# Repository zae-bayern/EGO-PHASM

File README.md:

Open-Source Repository für das BMWE-finanzierte Mikroprojekt "EGO-PHASM" des ZAE Bayerns.

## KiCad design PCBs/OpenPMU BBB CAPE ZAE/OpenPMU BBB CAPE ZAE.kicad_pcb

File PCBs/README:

These are the modified versions of the PCBs from OpenPMU. A brief overview of the changes:
- The sensor part has been adapted to 230V and 16A at 50Hz.
- The communication between sensor and measurement computer is digital now. All analog related circuitry is now on the Sensor Board only.
- The power and communication lines between the sensor board and the sensor cape has been secured with an isolation transformer and optocouplers.

The original OpenPMU project can be found here: https://www.openpmu.org/

It is highly recommended that this project is constructed and operated exclusively by qualified personnel!
This project is provided "as is" without any warranties, and the creators cannot be held liable for any direct or indirect damages.

(c) by T.Grassmann, ZAE Bayern e.V. licensed under the GNU GPL v3.
You should have received a copy of the license along with this work. If not, see <https://www.gnu.org/licenses/gpl-3.0.html>.

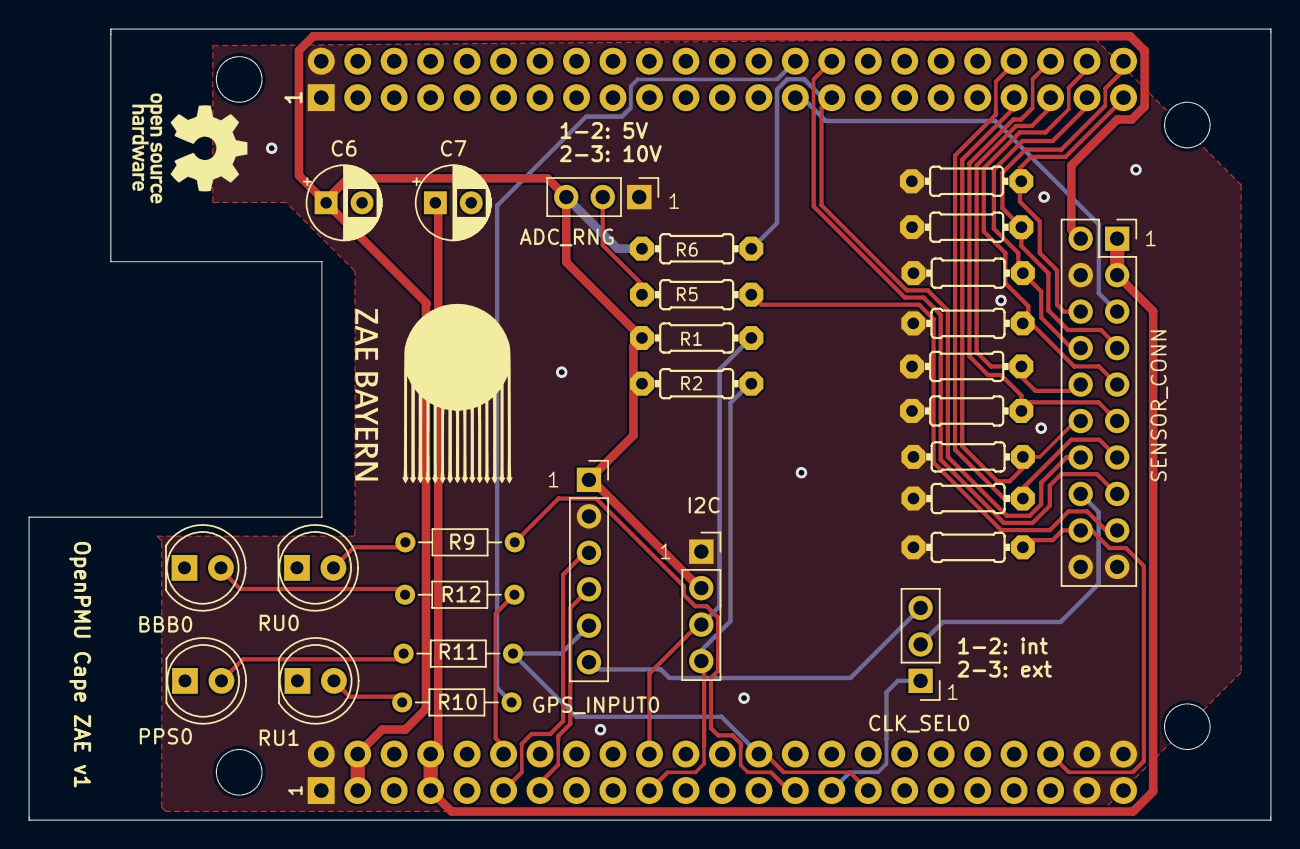
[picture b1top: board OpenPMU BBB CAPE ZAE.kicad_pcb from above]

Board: 2 copper layers, 86.5 x 55.1 mm, 29 parts (0 on the bottom side), 27 nets.

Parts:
BBB0: LEDCHIPLED_1206; LED_D5.0mm
C6, C7: CPOL-EUE1.8-4; CP_Radial_D5.0mm_P2.50mm
CLK_SEL0: JP2E; PinHeader_1x03_P2.54mm_Vertical
GPS_INPUT0: FE05-1; PinSocket_1x06_P2.54mm_Vertical
J1: Conn_01x20; PinSocket_2x10_P2.54mm_Vertical
J2: PINHD_1x4_Female; PinSocket_1x04_P2.54mm_Vertical
PPS0: LEDCHIPLED_1206; LED_D5.0mm
R1, R2, R5, R6, R7: 4.7k; 0204_7
R4, R8, R13, R14, R15, R16, R17, R18: 47k; 0204_7
R9, R10, R11, R12: R_Axial_DIN0204_L3.6mm_D1.6mm_P7.62mm_Horizontal
RNG_SEL0: JP2E; PinHeader_1x03_P2.54mm_Vertical
RU0, RU1: LEDCHIPLED_1206; LED_D5.0mm
U$1: BEAGLE_BONE_BLACK_CAPE; BEAGLE_BONE_BLACK_CAPE_509

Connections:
3.3V: GPS_INPUT0.1, J1.2, J2.2, R1.2, R2.2, R6.2, RNG_SEL0.3, U$1.P9.3, U$1.P9.4
5V: J1.1, J1.3, U$1.P9.7, U$1.P9.8
/BUSY: J1.14, R6.1, U$1.P8.29
/CONVST: CLK_SEL0.2, J1.16
/CONVST_OUT: CLK_SEL0.1, U$1.P9.29
/CS: J1.5, U$1.P8.27
/DB0: J1.6, R4.1, U$1.P8.45
/DB1: J1.7, R8.1, U$1.P8.46
/DB2: J1.8, R13.1, U$1.P8.43
/DB3: J1.9, R14.1, U$1.P8.44
/DB4: J1.10, R15.1, U$1.P8.41
/DB5: J1.11, R16.1, U$1.P8.42
/DB6: J1.12, R17.1, U$1.P8.39
/DB7: J1.13, R18.1, U$1.P8.40
/FRST: J1.18, R7.1, U$1.P9.42
/GPS_1PPS: GPS_INPUT0.5, R11.2, U$1.P9.26, U$1.P9.31
/GPS_RX: GPS_INPUT0.4, U$1.P9.13
/GPS_TX: GPS_INPUT0.3, U$1.P9.11
/LED_BBB: R12.2, U$1.P9.12
/LED_PRU0: R9.2, U$1.P9.27
/LED_PRU1: R10.2, U$1.P8.28
/RAGE: J1.17, R5.1
/RD: J1.15, U$1.P8.30
/RNG_SEL: R5.2, RNG_SEL0.2
/SCL: J2.4, R2.1, U$1.P9.19
/SDA: J2.3, R1.1, U$1.P9.20
GND: GPS_INPUT0.2, J1.4, J1.19, J1.20, J2.1, R4.2, R7.2, R8.2, R13.2, R14.2, R15.2, R16.2, R17.2, R18.2, RNG_SEL0.1, U$1.P8.1, U$1.P8.2, U$1.P9.1, U$1.P9.2, U$1.P9.43, U$1.P9.44, U$1.P9.45, U$1.P9.46

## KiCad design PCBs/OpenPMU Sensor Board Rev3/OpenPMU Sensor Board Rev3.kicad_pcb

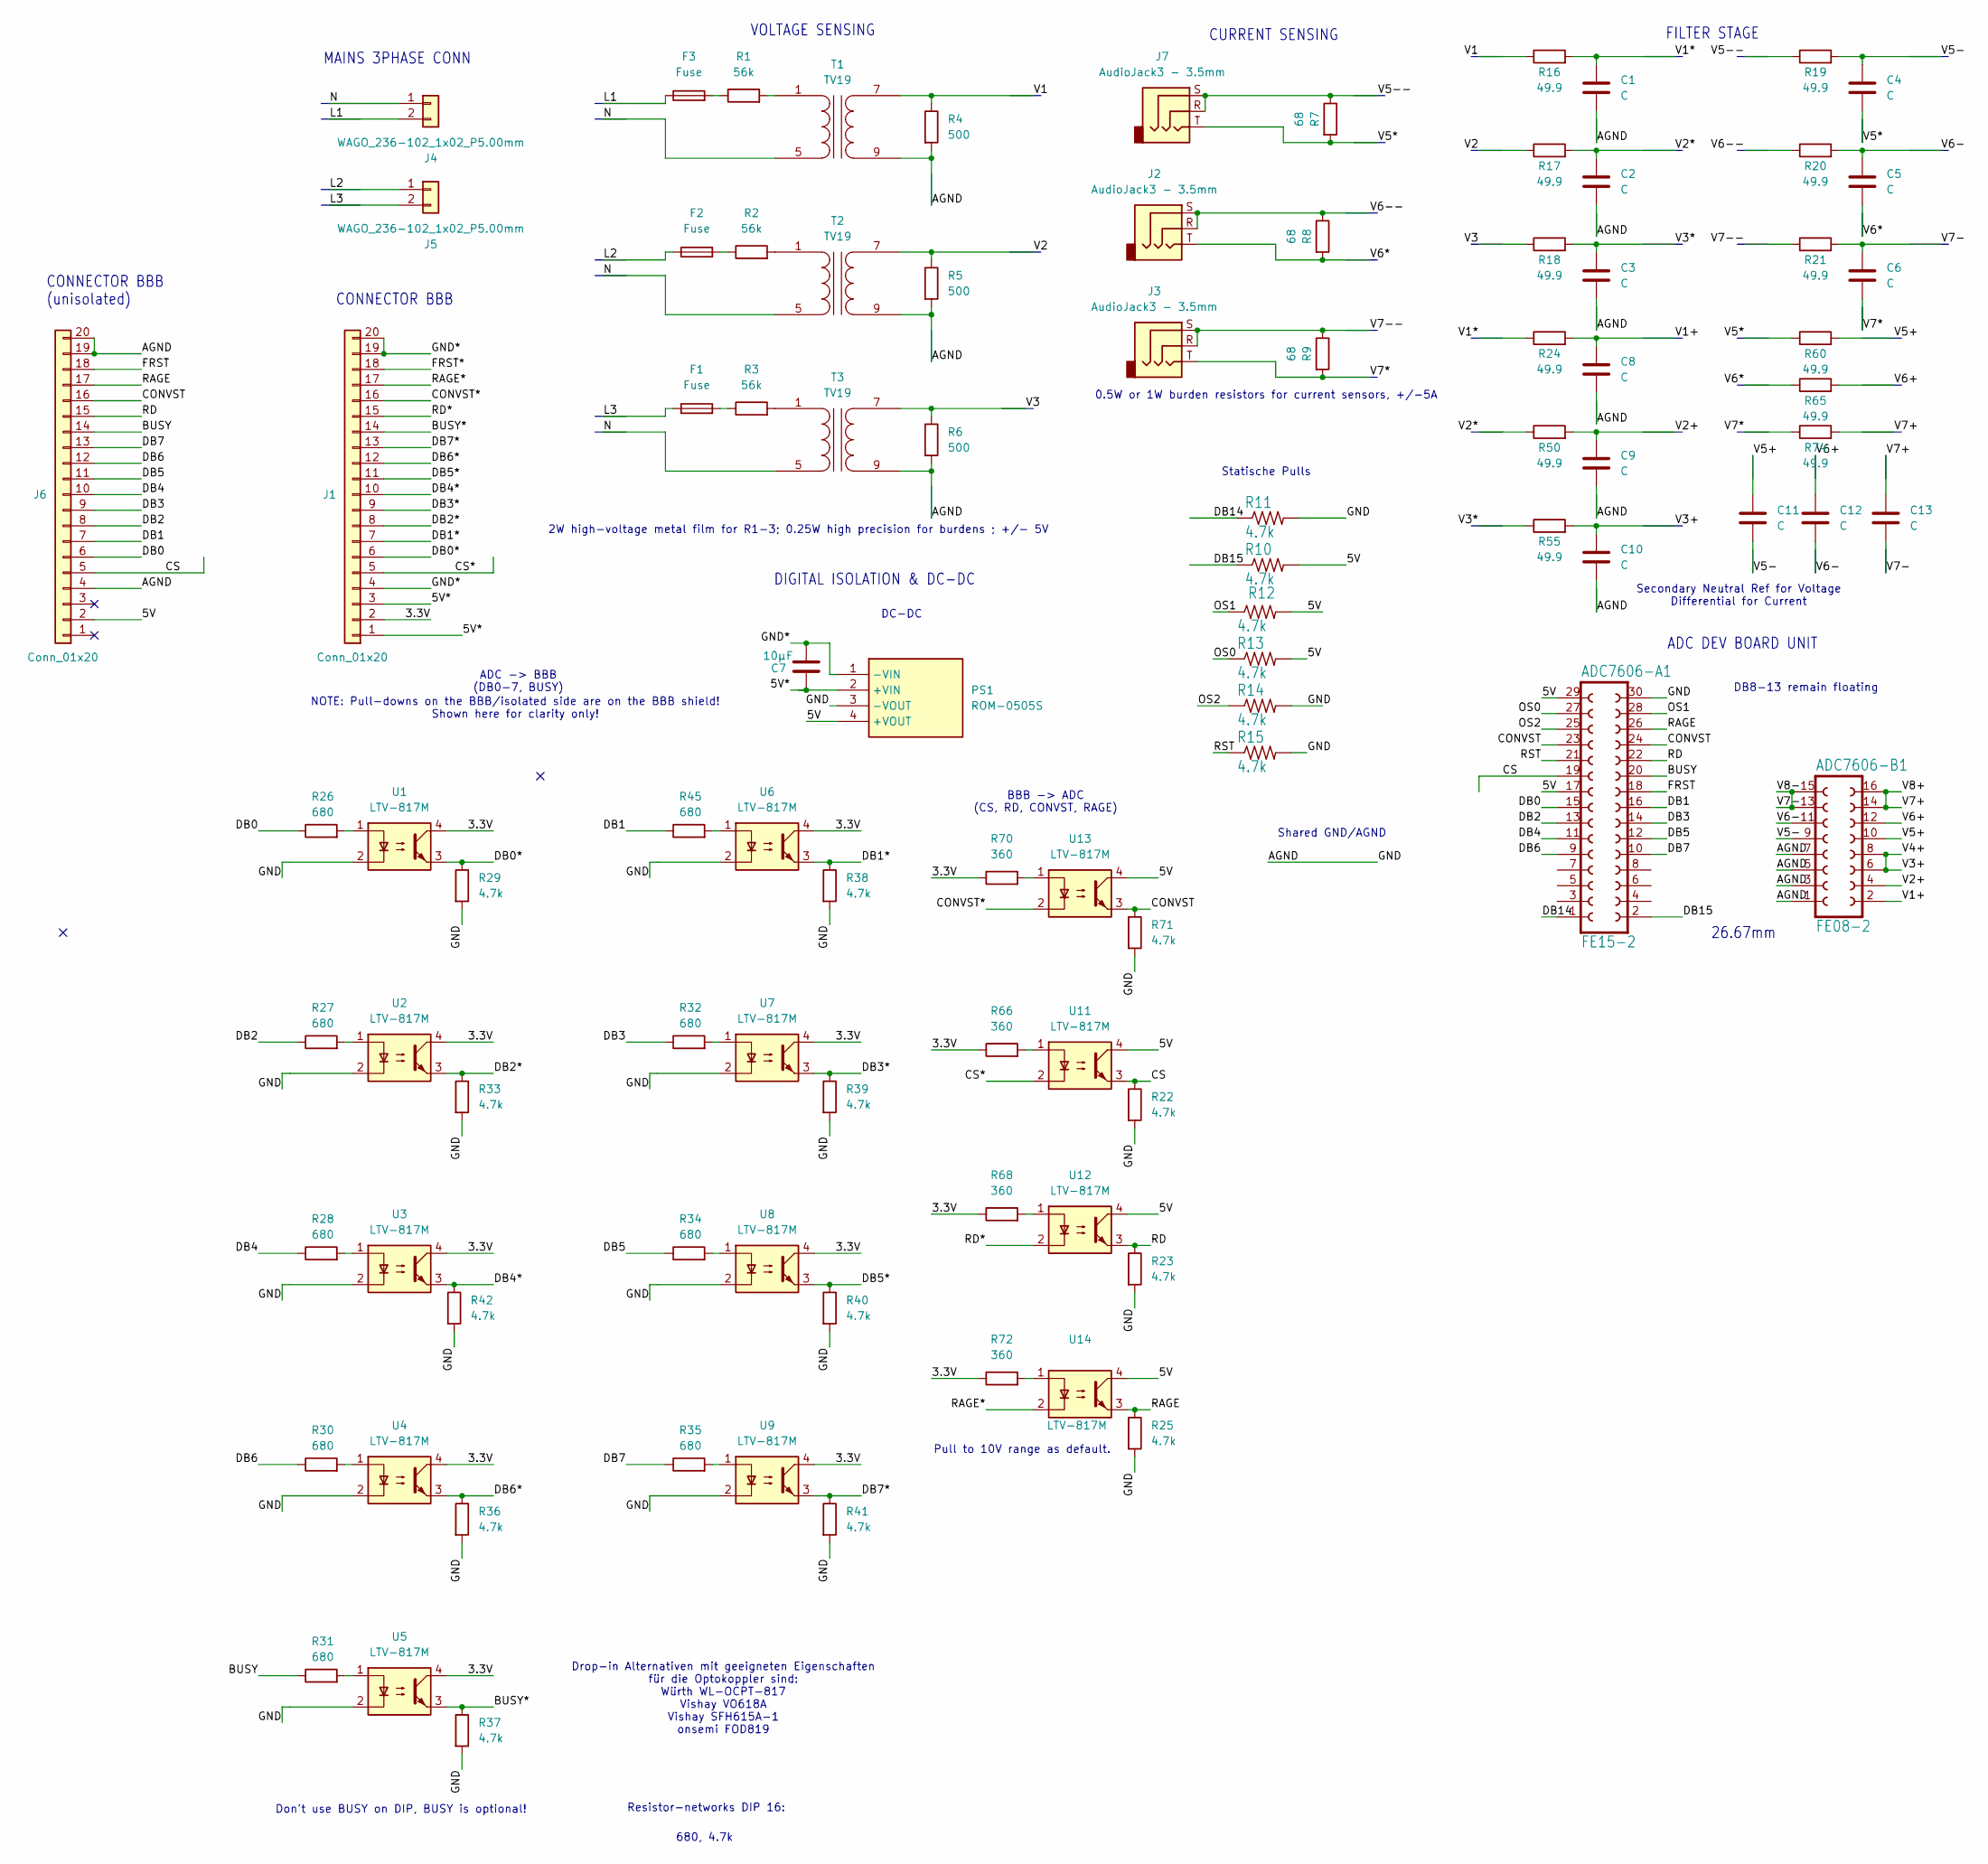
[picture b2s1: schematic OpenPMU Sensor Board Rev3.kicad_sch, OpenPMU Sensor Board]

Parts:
ADC7606-A1: FE15-2
ADC7606-B1: FE08-2
C1, C2, C3, C4, C5, C6, C8, C9, C10, C11, C12, C13: C; C_Disc_D4.7mm_W2.5mm_P5.00mm
C7: 10µF; C_Disc_D4.7mm_W2.5mm_P5.00mm
F1, F2, F3: Fuse; Fuseholder_Clip-5x20mm_Schurter_CQM_Inline_P20.60x5.00mm_D1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
J1, J6: Conn_01x20; PinSocket_2x10_P2.54mm_Vertical
J2, J3, J7: AudioJack3 - 3.5mm; Jack_3.5mm_CUI_SJ1-3523N_Horizontal
J4, J5: WAGO_236-102_1x02_P5.00mm; TerminalBlock_WAGO_236-102_1x02_P5.00mm_45Degree
PS1: ROM-0505S; Mouser Part Number 919-ROM-0505S
R1, R2, R3: 56k; R_Axial_DIN0411_L9.9mm_D3.6mm_P15.24mm_Horizontal
R4, R5, R6: 500; R_Axial_DIN0207_L6.3mm_D2.5mm_P10.16mm_Horizontal
R7, R8, R9: 68; R_Axial_DIN0207_L6.3mm_D2.5mm_P10.16mm_Horizontal
R10, R11, R12, R13, R14, R15, R22, R23, R25, R29, R33, R36, R37, R38, R39, R40, R41, R42, R71: 4.7k; R_Axial_DIN0207_L6.3mm_D2.5mm_P10.16mm_Horizontal
R16, R17, R18, R19, R20, R21, R24, R50, R55, R60, R65, R74: 49.9; R_Axial_DIN0207_L6.3mm_D2.5mm_P10.16mm_Horizontal
R26, R27, R28, R30, R31, R32, R34, R35, R45: 680; R_Axial_DIN0207_L6.3mm_D2.5mm_P10.16mm_Horizontal
R66, R68, R70, R72: 360; R_Axial_DIN0207_L6.3mm_D2.5mm_P10.16mm_Horizontal
T1, T2, T3: TV19; Transformer_TV19
U1, U2, U3, U4, U5, U6, U7, U8, U9, U11, U12, U13, U14: LTV-817M; DIP-4_W10.16mm

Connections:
/3.3V: J1.2, R66.1, R68.1, R70.1, R72.1, U1.4, U2.4, U3.4, U4.4, U5.4, U6.4, U7.4, U8.4, U9.4
/5V: ADC7606-A1.17, ADC7606-A1.29, J6.2, PS1.4 (+VOUT), R10.2, R12.2, R13.2, U11.4, U12.4, U13.4, U14.4
/5V*: C7.2, J1.1, J1.3, PS1.2 (+VIN)
/BUSY: ADC7606-A1.20, J6.14, R31.1
/BUSY*: J1.14, R37.1, U5.3
/CONVST: ADC7606-A1.23, ADC7606-A1.24, J6.16, R71.1, U13.3
/CONVST*: J1.16, U13.2
/CS: ADC7606-A1.19, J6.5, R22.1, U11.3
/CS*: J1.5, U11.2
/DB0: ADC7606-A1.15, J6.6, R26.1
/DB0*: J1.6, R29.1, U1.3
/DB1: ADC7606-A1.16, J6.7, R45.1
/DB1*: J1.7, R38.1, U6.3
/DB2: ADC7606-A1.13, J6.8, R27.1
/DB2*: J1.8, R33.1, U2.3
/DB3: ADC7606-A1.14, J6.9, R32.1
/DB3*: J1.9, R39.1, U7.3
/DB4: ADC7606-A1.11, J6.10, R28.1
/DB4*: J1.10, R42.1, U3.3
/DB5: ADC7606-A1.12, J6.11, R34.1
/DB5*: J1.11, R40.1, U8.3
/DB6: ADC7606-A1.9, J6.12, R30.1
/DB6*: J1.12, R36.1, U4.3
/DB7: ADC7606-A1.10, J6.13, R35.1
/DB7*: J1.13, R41.1, U9.3
/DB14: ADC7606-A1.1, R11.1
/DB15: ADC7606-A1.2, R10.1
/FRST*: J1.18
/GND*: C7.1, J1.4, J1.19, J1.20, PS1.1 (-VIN)
/L1: F3.1, J4.2
/L2: F2.1, J5.1
/L3: F1.1, J5.2
/N: J4.1, T1.5 (AB), T2.5 (AB), T3.5 (AB)
/OS0: ADC7606-A1.27, R13.1
/OS1: ADC7606-A1.28, R12.1
/OS2: ADC7606-A1.25, R14.1
/RAGE: ADC7606-A1.26, J6.17, R25.1, U14.3
/RAGE*: J1.17, U14.2
/RD: ADC7606-A1.22, J6.15, R23.1, U12.3
/RD*: J1.15, U12.2
/RST: ADC7606-A1.21, R15.1
/V1: R4.1, R16.1, T1.7 (SB)
/V1*: C1.1, R16.2, R24.1
/V1+: ADC7606-B1.2, C8.1, R24.2
/V2: R5.1, R17.1, T2.7 (SB)
/V2*: C2.1, R17.2, R50.1
/V2+: ADC7606-B1.4, C9.1, R50.2
/V3: R6.1, R18.1, T3.7 (SB)
/V3*: C3.1, R18.2, R55.1
/V3+: ADC7606-B1.6, ADC7606-B1.8, C10.1, R55.2
/V5*: C4.2, J7.T, R7.2, R60.1
/V5+: ADC7606-B1.10, C11.1, R60.2
/V5-: ADC7606-B1.9, C4.1, C11.2, R19.2
/V5--: J7.R, J7.S, R7.1, R19.1
/V6*: C5.2, J2.T, R8.2, R65.1
/V6+: ADC7606-B1.12, C12.1, R65.2
/V6-: ADC7606-B1.11, C5.1, C12.2, R20.2
/V6--: J2.R, J2.S, R8.1, R20.1
/V7*: C6.2, J3.T, R9.2, R74.1
/V7+: ADC7606-B1.14, ADC7606-B1.16, C13.1, R74.2
/V7-: ADC7606-B1.13, ADC7606-B1.15, C6.1, C13.2, R21.2
/V7--: J3.R, J3.S, R9.1, R21.1
unnamed: F1.2, R3.1
unnamed: F2.2, R2.1
unnamed: F3.2, R1.1
unnamed: R26.2, U1.1
unnamed: R27.2, U2.1
unnamed: R28.2, U3.1
unnamed: R30.2, U4.1
unnamed: R31.2, U5.1
unnamed: R32.2, U7.1
unnamed: R34.2, U8.1
unnamed: R35.2, U9.1
unnamed: R45.2, U6.1
unnamed: R66.2, U11.1
unnamed: R68.2, U12.1
unnamed: R70.2, U13.1
unnamed: R72.2, U14.1
unnamed: R1.2, T1.1 (AA)
unnamed: R2.2, T2.1 (AA)
unnamed: R3.2, T3.1 (AA)

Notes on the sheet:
MAINS 3PHASE CONN
NOTE: Pull-downs on the BBB/isolated side are on the BBB shield! Shown here for clarity only!
Don't use BUSY on DIP, BUSY is optional!
Pull to 10V range as default.
680, 4.7k
CONNECTOR BBB (unisolated)
FILTER STAGE
VOLTAGE SENSING
0.5W or 1W burden resistors for current sensors, +/-5A
ADC DEV BOARD UNIT
DC-DC
Resistor-networks DIP 16:
Shared GND/AGND
CURRENT SENSING
Statische Pulls
26.67mm
ADC -> BBB (DB0-7, BUSY)
DIGITAL ISOLATION & DC-DC
BBB -> ADC (CS, RD, CONVST, RAGE)
Drop-in Alternativen mit geeigneten Eigenschaften für die Optokoppler sind: Würth WL-OCPT-817 Vishay VO618A Vishay SFH615A-1 onsemi FOD819
2W high-voltage metal film for R1-3; 0.25W high precision for burdens ; +/- 5V
Secondary Neutral Ref for Voltage Differential for Current
DB8-13 remain floating
CONNECTOR BBB

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
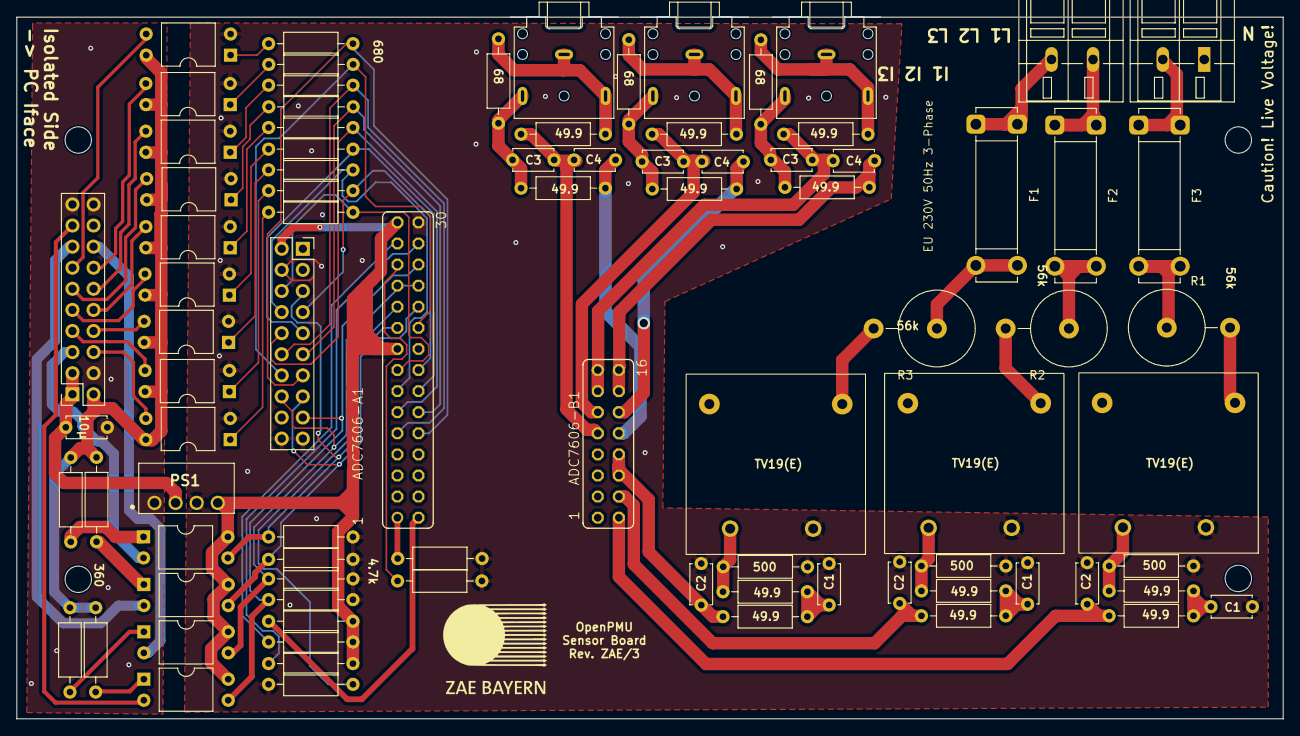
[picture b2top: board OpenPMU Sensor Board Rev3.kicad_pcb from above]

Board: 2 copper layers, 152.4 x 84.5 mm, 86 parts (0 on the bottom side), 82 nets.

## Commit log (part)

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2026-02-26 Add README for EGO-PHASM project
